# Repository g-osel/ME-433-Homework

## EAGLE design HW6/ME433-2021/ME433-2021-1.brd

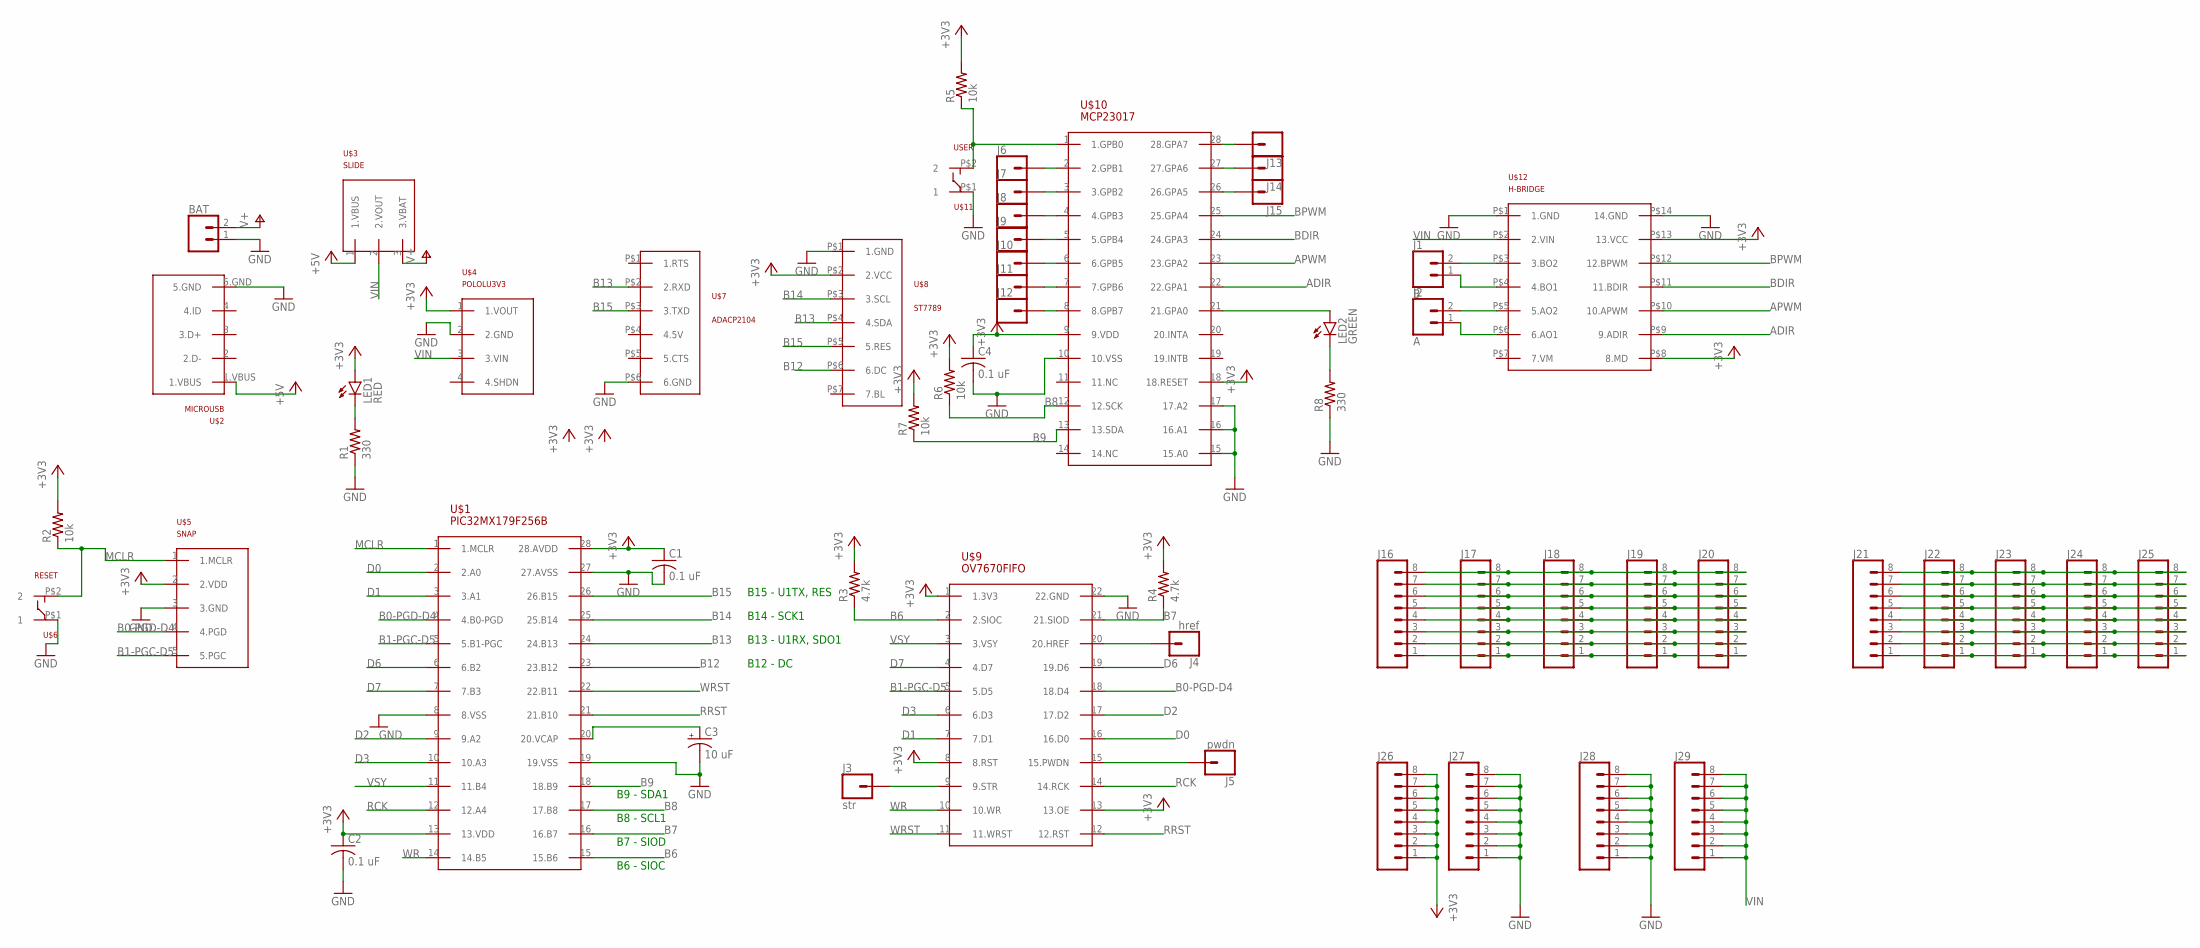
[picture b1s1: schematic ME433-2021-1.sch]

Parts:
BAT: CONN_02; 1X02
C1, C2, C4: 0.1 uF; C025-030X050
C3: 10 uF; B45181B
J1: B; 1X02
J2: A; 1X02
J3: str; 1X01
J4: href; 1X01
J5: pwdn; 1X01
J6, J7, J8, J9, J10, J11, J12, J13, J14, J15: CONN_01; 1X01
J16, J17, J18, J19, J20, J21, J22, J23, J24, J25, J26, J27, J28, J29: CONN_08"; 1X08
LED1: RED; LED3MM
LED2: GREEN; LED3MM
R1, R8: 330; 0207/10
R2, R5, R6, R7: 10k; 0207/10
R3, R4: 4.7k; 0207/10
U$1: PIC32MX179F256B; DIL28-3
U$2: MICROUSB
U$3: SLIDE
U$4: POLOLU3V3
U$5: SNAP
U$6: RESET; PUSH
U$7: ADACP2104
U$8: ST7789
U$9: OV7670FIFO
U$10: MCP23017; DIL28-3
U$11: USER; PUSH
U$12: H-BRIDGE

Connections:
+3V3: C1.1, C2.1, C4.1, J26.1, J26.2, J26.3, J26.4, J26.5, J26.6, J26.7, J26.8, LED1.A, R2.2, R3.2, R4.2, R5.2, R6.2, R7.2, U$1.13 (13.VDD), U$1.28 (28.AVDD), U$4.1 (1.VOUT), U$5.2 (2.VDD), U$8.P$2 (2.VCC), U$9.1 (1.3V3), U$9.8 (8.RST), U$9.13 (13.OE), U$10.9 (9.VDD), U$10.18 (18.RESET), U$12.P$8 (8.MD), U$12.P$13 (13.VCC)
+5V: U$2.1.VBUS, U$3.1 (1.VBUS)
ADIR: U$10.22 (22.GPA1), U$12.P$9 (9.ADIR)
APWM: U$10.23 (23.GPA2), U$12.P$10 (10.APWM)
B0-PGD-D4: U$1.4 (4.B0-PGD), U$5.4 (4.PGD), U$9.18 (18.D4)
B1-PGC-D5: U$1.5 (5.B1-PGC), U$5.5 (5.PGC), U$9.5 (5.D5)
B6: R3.1, U$1.15 (15.B6), U$9.2 (2.SIOC)
B7: R4.1, U$1.16 (16.B7), U$9.21 (21.SIOD)
B8: R6.1, U$1.17 (17.B8), U$10.12 (12.SCK)
B9: R7.1, U$1.18 (18.B9), U$10.13 (13.SDA)
B12: U$1.23 (23.B12), U$8.P$6 (6.DC)
B13: U$1.24 (24.B13), U$7.P$2 (2.RXD), U$8.P$4 (4.SDA)
B14: U$1.25 (25.B14), U$8.P$3 (3.SCL)
B15: U$1.26 (26.B15), U$7.P$3 (3.TXD), U$8.P$5 (5.RES)
BDIR: U$10.24 (24.GPA3), U$12.P$11 (11.BDIR)
BPWM: U$10.25 (25.GPA4), U$12.P$12 (12.BPWM)
D0: U$1.2 (2.A0), U$9.16 (16.D0)
D1: U$1.3 (3.A1), U$9.7 (7.D1)
D2: U$1.9 (9.A2), U$9.17 (17.D2)
D3: U$1.10 (10.A3), U$9.6 (6.D3)
D6: U$1.6 (6.B2), U$9.19 (19.D6)
D7: U$1.7 (7.B3), U$9.4 (4.D7)
GND: BAT.1, C1.2, C2.2, C3.-, C4.2, J27.1, J27.2, J27.3, J27.4, J27.5, J27.6, J27.7, J27.8, J28.1, J28.2, J28.3, J28.4, J28.5, J28.6, J28.7, J28.8, R1.1, R8.1, U$1.8 (8.VSS), U$1.19 (19.VSS), U$1.27 (27.AVSS), U$2.5.GND, U$4.2 (2.GND), U$5.3 (3.GND), U$6.P$1 (1), U$7.P$6 (6.GND), U$8.P$1 (1.GND), U$9.22 (22.GND), U$10.10 (10.VSS), U$10.15 (15.A0), U$10.16 (16.A1), U$10.17 (17.A2), U$11.P$1 (1), U$12.P$1 (1.GND), U$12.P$14 (14.GND)
MCLR: R2.1, U$1.1 (1.MCLR), U$5.1 (1.MCLR), U$6.P$2 (2)
unnamed: LED1.K (C), R1.2
unnamed: C3.+, U$1.20 (20.VCAP)
unnamed: J3.1, U$9.9 (9.STR)
unnamed: R5.1, U$10.1 (1.GPB0), U$11.P$2 (2)
unnamed: LED2.A, U$10.21 (21.GPA0)
unnamed: LED2.K (C), R8.2
unnamed: J6.1, U$10.2 (2.GPB1)
unnamed: J7.1, U$10.3 (3.GPB2)
unnamed: J1.2, U$12.P$3 (3.BO2)
unnamed: J4.1, U$9.20 (20.HREF)
unnamed: J1.1, U$12.P$4 (4.BO1)
unnamed: J2.2, U$12.P$5 (5.AO2)
unnamed: J2.1, U$12.P$6 (6.AO1)
unnamed: J8.1, U$10.4 (4.GPB3)
unnamed: J5.1, U$9.15 (15.PWDN)
unnamed: J9.1, U$10.5 (5.GPB4)
unnamed: J10.1, U$10.6 (6.GPB5)
unnamed: J11.1, U$10.7 (7.GPB6)
unnamed: J12.1, U$10.8 (8.GPB7)
unnamed: J13.1, U$10.28 (28.GPA7)
unnamed: J14.1, U$10.27 (27.GPA6)
unnamed: J15.1, U$10.26 (26.GPA5)
unnamed: J16.8, J17.8, J18.8, J19.8, J20.8
unnamed: J16.7, J17.7, J18.7, J19.7, J20.7
unnamed: J16.6, J17.6, J18.6, J19.6, J20.6
unnamed: J16.5, J17.5, J18.5, J19.5, J20.5
unnamed: J16.4, J17.4, J18.4, J19.4, J20.4
unnamed: J16.3, J17.3, J18.3, J19.3, J20.3
unnamed: J16.2, J17.2, J18.2, J19.2, J20.2
unnamed: J16.1, J17.1, J18.1, J19.1, J20.1
unnamed: J21.8, J22.8, J23.8, J24.8, J25.8
unnamed: J21.7, J22.7, J23.7, J24.7, J25.7
unnamed: J21.5, J22.5, J23.5, J24.5, J25.5
unnamed: J21.6, J22.6, J23.6, J24.6, J25.6
unnamed: J21.4, J22.4, J23.4, J24.4, J25.4
unnamed: J21.3, J22.3, J23.3, J24.3, J25.3
unnamed: J21.2, J22.2, J23.2, J24.2, J25.2
unnamed: J21.1, J22.1, J23.1, J24.1, J25.1
RCK: U$1.12 (12.A4), U$9.14 (14.RCK)
RRST: U$1.21 (21.B10), U$9.12 (12.RST)
V+: BAT.2, U$3.3 (3.VBAT)
VIN: J29.1, J29.2, J29.3, J29.4, J29.5, J29.6, J29.7, J29.8, U$3.2 (2.VOUT), U$4.3 (3.VIN), U$12.P$2 (2.VIN)
VSY: U$1.11 (11.B4), U$9.3 (3.VSY)
WR: U$1.14 (14.B5), U$9.10 (10.WR)
WRST: U$1.22 (22.B11), U$9.11 (11.WRST)

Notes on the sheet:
B15 - U1TX, RES
B14 - SCK1
B13 - U1RX, SDO1
B12 - DC
B9 - SDA1
B8 - SCL1
B7 - SIOD
B6 - SIOC

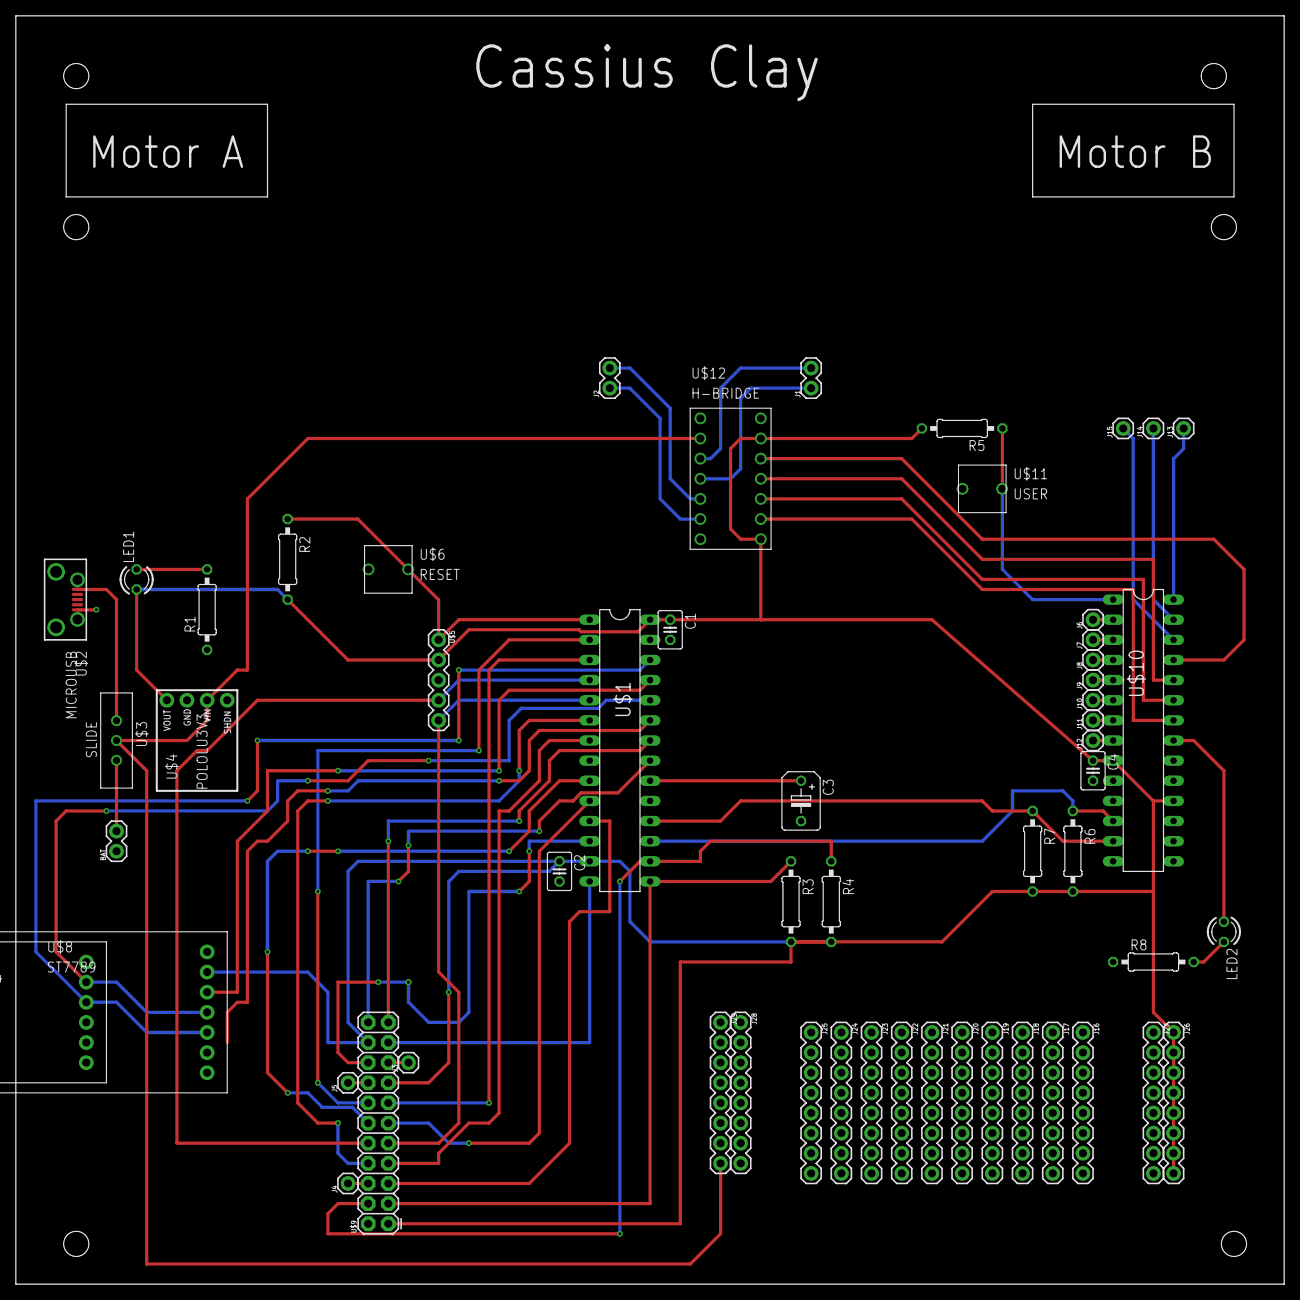
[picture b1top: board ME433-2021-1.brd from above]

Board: 2 copper layers, 160.0 x 160.0 mm, 56 parts (0 on the bottom side), 69 nets.

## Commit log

2021-04-06 Adding files for homework submission
2021-04-09 Updated plots pdf
2021-04-16 Submitting HW4
2021-04-16 added a delay function
2021-04-16 Submission for HW5
2021-05-11 Submitting homeworks
2021-05-17 homework submissions
2021-06-10 Submissions

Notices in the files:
parts and their libraries:
SparkFun-Connectors: Licensing: Creative Commons ShareAlike 4.0 International - https://creativecommons.org/licenses/by-sa/4.0
